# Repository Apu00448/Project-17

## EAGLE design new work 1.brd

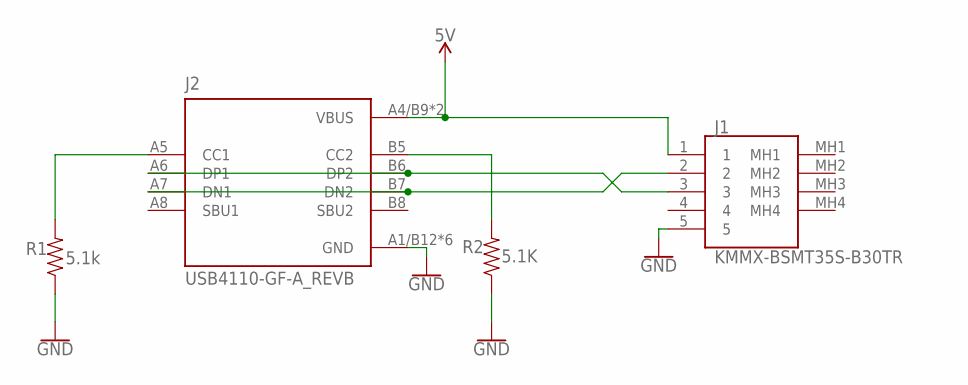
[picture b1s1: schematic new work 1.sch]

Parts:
J1: KMMX-BSMT35S-B30TR; KMMXBSMT35SB30TR
J2: USB4110-GF-A_REVB; GCT_USB4110-GF-A_REVB
R1: 5.1k; 0402-TIGHT
R2: 5.1K; 0402-TIGHT

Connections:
5V: J1.1, J2.A4/B9 (VBUS), J2.B4/A9 (VBUS)
GND: J1.5, J2.A1/B12 (GND), J2.B1/A12 (GND), J2.S1 (GND), J2.S2 (GND), J2.S3 (GND), J2.S4 (GND), R1.1, R2.1
unnamed: J1.3, J2.A6 (DP1), J2.B6 (DP2)
unnamed: J1.2, J2.A7 (DN1), J2.B7 (DN2)
unnamed: J2.B5 (CC2), R2.2
unnamed: J2.A5 (CC1), R1.2

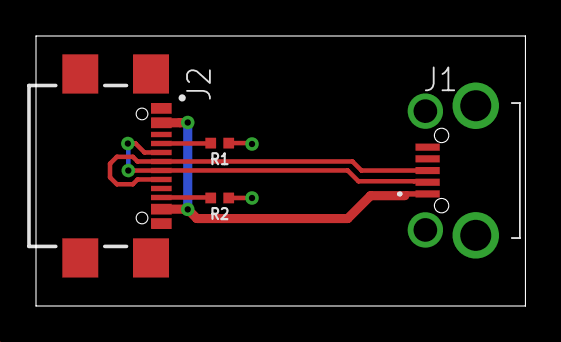
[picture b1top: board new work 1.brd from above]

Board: 2 copper layers, 27.2 x 15.0 mm, 4 parts (0 on the bottom side), 6 nets.

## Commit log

2024-01-03 USB to Micro USB- Eagle

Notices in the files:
parts and their libraries:
SparkFun-Resistors: Licensing: Creative Commons ShareAlike 4.0 International - https://creativecommons.org/licenses/by-sa/4.0
